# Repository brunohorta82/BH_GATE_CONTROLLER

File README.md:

# BH GATE CONTROLLER

* [Intro](#id1)
* [Firmware](https://github.com/brunohorta82/easy_iot)
* [Donativos](#id6)

## Intro 
O BH GATE permite controlar cargas até 30V o que o torna perfeito para controlar portões electricos. A Placa tem suporte até 3 relés REED. É possivel controlar motores que têm interfaces de controlo distintas para Abrir, Fechar e Parar. Para controlar portões em que só utilizam uma interface para controlar todos os estados basta utilizar apenas um relé. A PCB ainda vem com 2 entradas para sensores magnéticos e uma entrada analógica para instalar um sensor de luz (LDR).

## Donativos 

Se gostaste do projeto podes fazer o teu donativo :).

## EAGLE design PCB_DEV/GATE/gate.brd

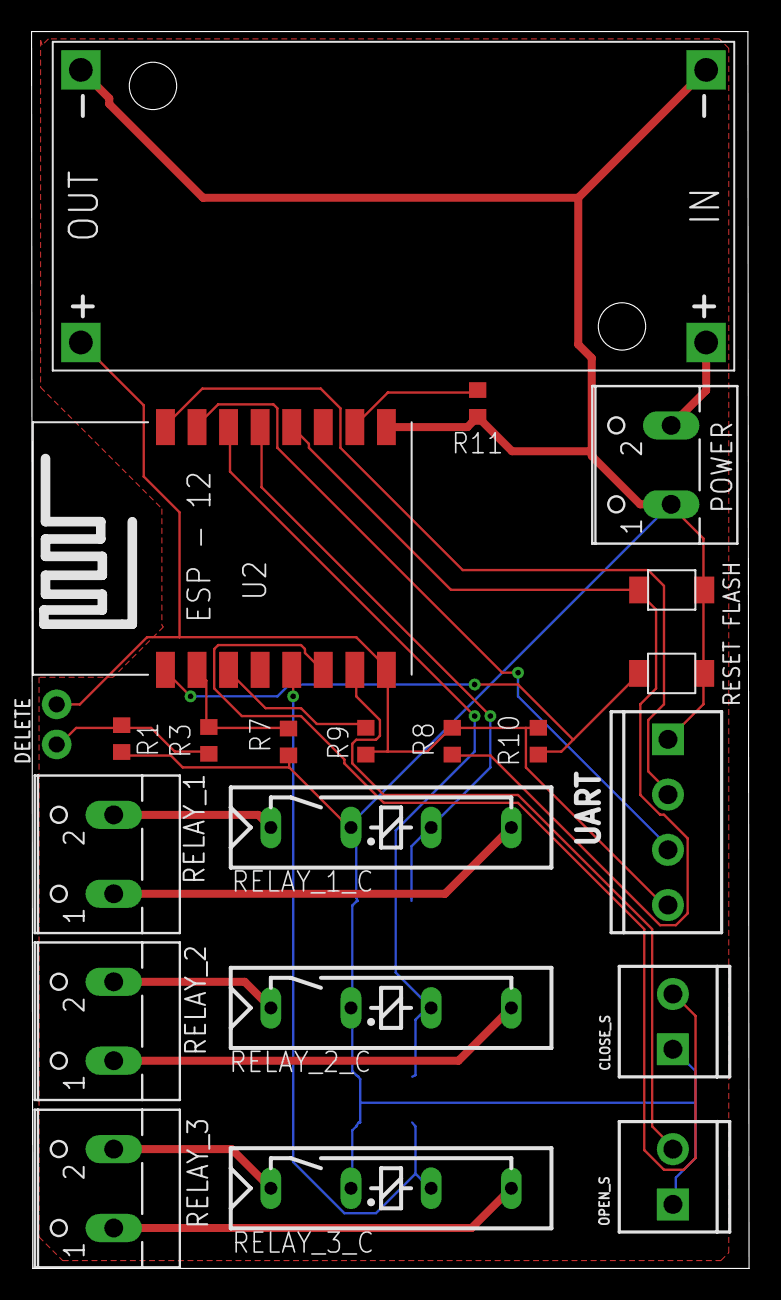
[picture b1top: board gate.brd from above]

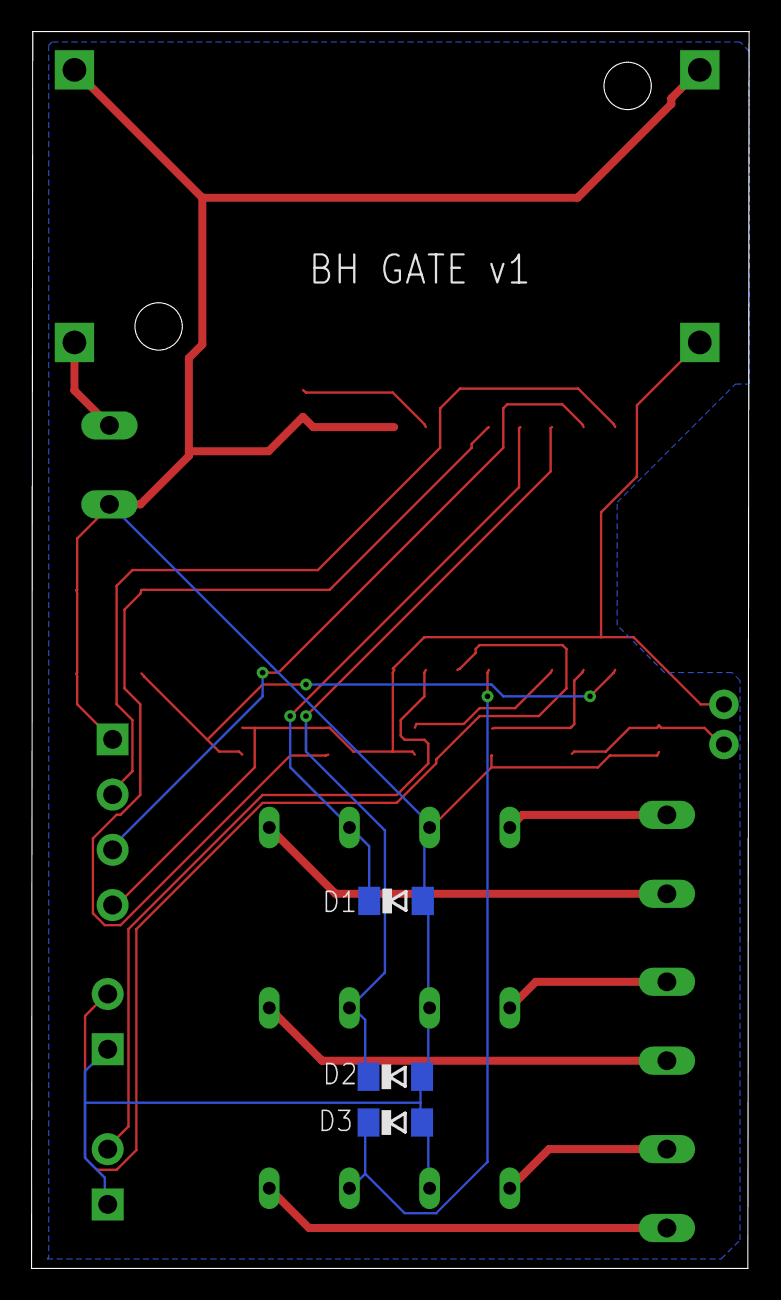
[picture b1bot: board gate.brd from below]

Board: 2 copper layers, 45.5 x 78.4 mm, 25 parts (3 on the bottom side), 22 nets.

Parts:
CLOSE_S: SCREWTERMINAL-3.5MM-2
D1, D2, D3: 1N4148; SOD80C
FLASH: B3U-1000P-2P-SMD; B3U-1000P
LDR: LDR-TH; 1X02
OPEN_S: SCREWTERMINAL-3.5MM-2
POWER: W237-102
R1, R8, R9, R10, R11: 10k; R0603
R3: 220k; R0603
R7: 100k; R0603
RELAY_1, RELAY_2, RELAY_3: W237-102
RELAY_1_C, RELAY_2_C, RELAY_3_C: REED
RESET: B3U-1000P-2P-SMD; B3U-1000P
U2: esp12; ESP12-SMD
U$1: DC-DC-STEP-DOWN-LM2596
UART: SCREWTERMINAL-3.5MM-4

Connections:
3V3: LDR.2, R8.2, R9.2, R10.2, U2.VCC, U$1.OUT+, UART.4
A0: LDR.1, R1.1, R3.2
ADC: R3.1, R7.2, U2.ADC
CH_PD: R9.1, U2.CH_PD
GND: CLOSE_S.1, D1.A, D2.A, D3.A, FLASH.2, OPEN_S.1, POWER.1, R1.2, R7.1, R11.2, RELAY_1_C.3, RELAY_2_C.3, RELAY_3_C.3, RESET.2, U2.GND, U$1.IN-, U$1.OUT-, UART.1
GND1: RELAY_1.1, RELAY_1_C.7
GND2: RELAY_2.1, RELAY_2_C.7
GND3: RELAY_3.1, RELAY_3_C.7
GPIO0: FLASH.1, R8.1, U2.GPIO0
GPIO04: D1.C, RELAY_1_C.5, U2.GPIO4
GPIO05: D2.C, RELAY_2_C.5, U2.GPIO5
GPIO12: CLOSE_S.2, U2.GPIO12
GPIO13: OPEN_S.2, U2.GPIO13
GPIO14: D3.C, RELAY_3_C.5, U2.GPIO14
GPIO15: R11.1, U2.GPIO15
unnamed: RELAY_1.2, RELAY_1_C.1
unnamed: RELAY_2.2, RELAY_2_C.1
unnamed: RELAY_3.2, RELAY_3_C.1
unnamed: POWER.2, U$1.IN+
RESET: R10.1, RESET.1, U2.RESET
RX: U2.RXD0, UART.3
TX: U2.TXD0, UART.2

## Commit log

2019-03-27 pcb in dev
2019-03-28 pcb done v1
2019-03-28 clean v1
2019-03-29 gate
2019-04-08 V1
    V1
2020-01-28 PCB V2.0

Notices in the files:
parts and their libraries:
SparkFun-Connectors: Licensing: Creative Commons ShareAlike 4.0 International - https://creativecommons.org/licenses/by-sa/4.0
diy-modules: Released under the Creative Commons Attribution 4.0 International License: http://creativecommons.org/licenses/by/4.0
